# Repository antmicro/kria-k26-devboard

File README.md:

# Antmicro's open source Kria K26 Devboard

Copyright (c) 2022-2023 [Antmicro](https://www.antmicro.com)

## Overview

This project contains open hardware design files for a devkit created for AMD-Xilinx [Kria K26](https://www.xilinx.com/products/som/kria.html) System on Module (SoM).

This development board routes the I/O interfaces from the SoM and provides the necessary power buses.
The design files were prepared in KiCad 7.

## Project structure

The main directory contains KiCad PCB project files, a [LICENSE](LICENSE), and a README.
The remaining files are stored in the following directories:

* `lib` - contains the component libraries
* `img` - contains graphics for this README
* `doc` - contains schematics in pdf form
* `assets` - contains visual assets for showcasing this design on [Open Hardware Portal](https://openhardware.antmicro.com).

## Key Features

* AMD-Xilinx Kria K26 SOM
* Gigabit Ethernet
* DisplayPort output
* 4x USB 3.2 Gen 1 connector
* USB Type-C connector for FTDI JTAG and debug
* M.2 connector (key E) for optional WiFi and Bluetooth connectivity
* 2x 4-lane MIPI CSI-2 camera interface
* PMOD
* SD 3.0 (MicroSD UHS-1)

The board supports multiple power supply scenarios, including:

* PoE (Power over Ethernet)
* USB-C PD (Power Delivery)
* External PSU via DC Jack

The on-board camera connector is electrically compatible with several video accessories created by Antmicro, such as:
 
* [OV9281 Dual Camera Board](https://github.com/antmicro/ov9281-camera-board)
* [SDI-MIPI bridge](https://github.com/antmicro/sdi-mipi-bridge)
* [HDMI-MIPI bridge](https://github.com/antmicro/hdmi-mipi-bridge)

## Block diagram

## License

This project is published under the [Apache-2.0](LICENSE) license.

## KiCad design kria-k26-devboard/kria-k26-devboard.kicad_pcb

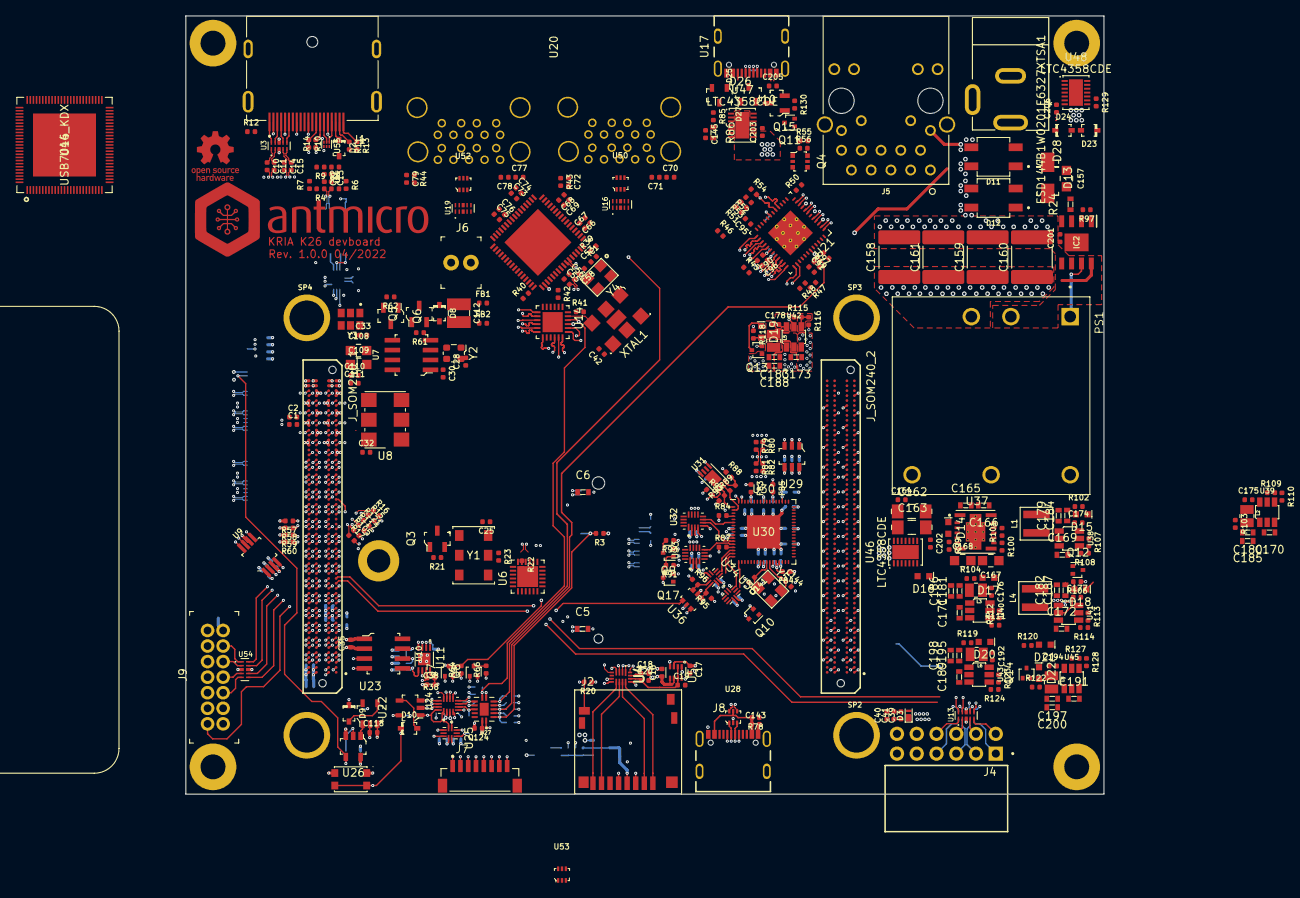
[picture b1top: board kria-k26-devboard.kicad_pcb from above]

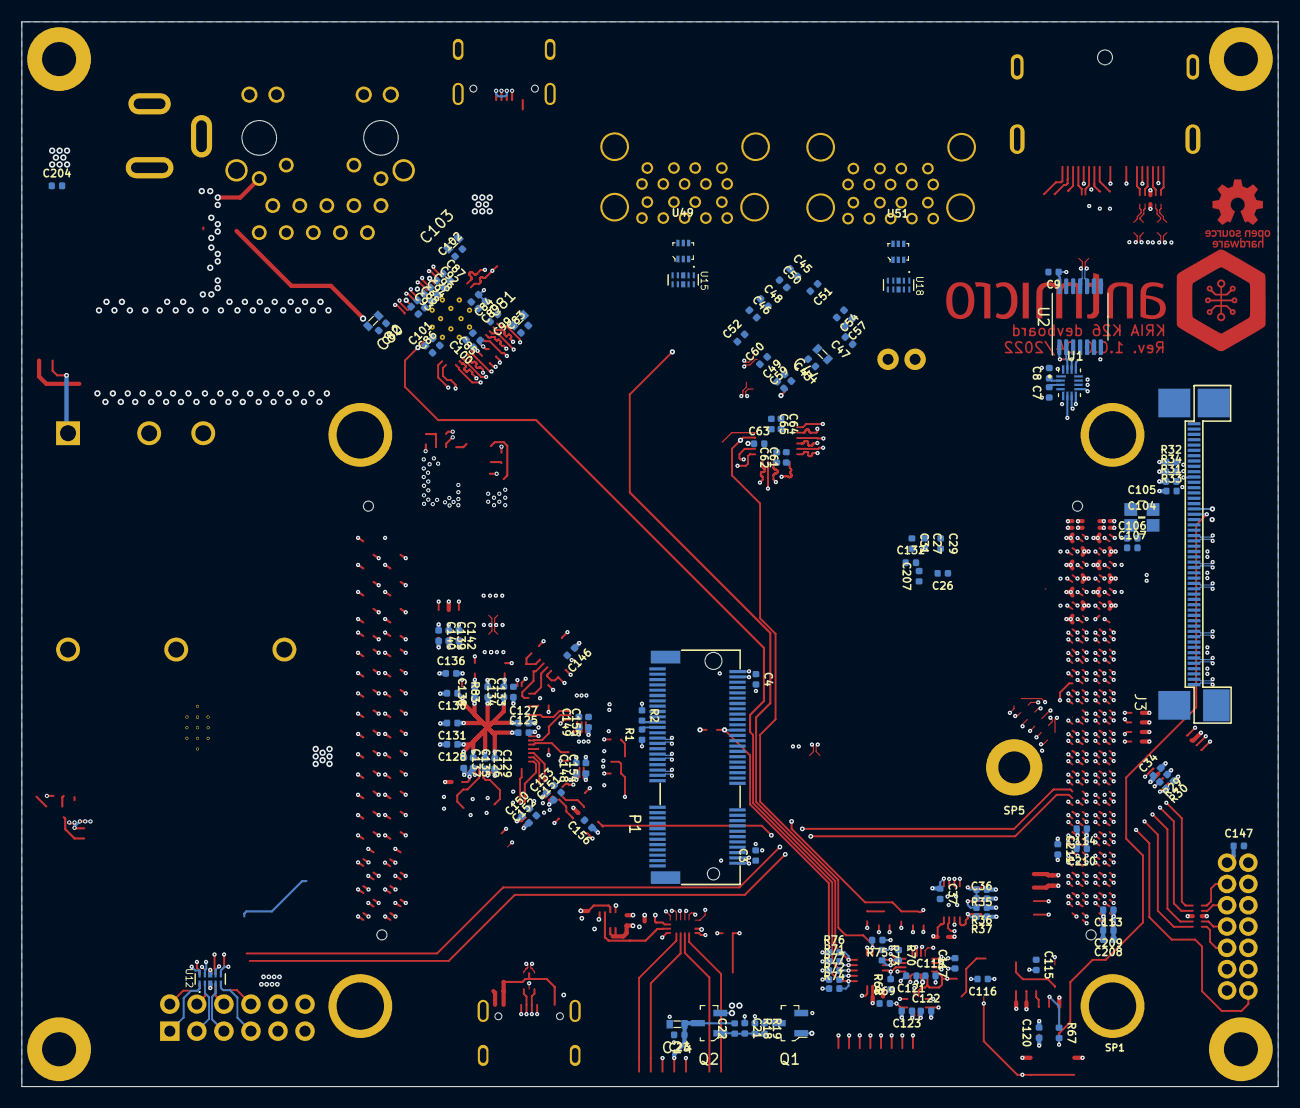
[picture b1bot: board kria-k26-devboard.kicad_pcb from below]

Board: 8 copper layers, 118.0 x 100.0 mm, 469 parts (140 on the bottom side), 378 nets.

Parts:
C1, C2, C3, C4, C7, C8, C9, C10, C11, C12, C13, C14, C15, C16, C17, C18, C19, C20, C23, C25, C26, C27, C28, C29, C30, C31, C32, C33, C34, C35, C37, C38, C40, C41, C42, C45, C46, C47, C48, C49, C50, C51, C52, C54, C55, C56, C57, C59, C60, C61, C62, C63, C65, C66, C67, C68, C69, C72, C73, C74, C75, C76, C79, C89, C90, C91, C92, C93, C94, C95, C96, C97, C107, C111, C113, C114, C117, C118, C119, C120, C121, C122, C123, C124, C125, C126, C127, C128, C129, C130, C131, C132, C133, C134, C135, C137, C138, C139, C140, C142, C146, C147, C148, C149, C150, C151, C152, C153, C154, C155, C156, C174, C175, C176, C177, C178, C192, C194, C201, C202, C203, C204, C207, C209, C211: C_100n_0402; 0402-cap
C5, C6, C24, C44, C80, C81, C103: C_10u_0603; 0603-cap
C21, C22: C_470n_0402; 0402-cap
C36: C_100p_0402; 0402-cap
C39, C43, C84, C85, C86, C87, C88, C98, C99, C100, C101, C106, C110: C_1u_0402; 0402-cap
C53, C58, C141, C144: C_18p_0402; 0402-cap
C64: C_2u2_0402; 0402-cap
C70, C71, C77, C78, C136, C208, C210: C_4u7_0402; 0402-cap
C82, C83, C102: C_10n_0402; 0402-cap
C104, C105, C108, C109, C167, C168: C_47u_0805; 0805-cap
C112: C_1u_1210_100V; 1210-cap
C115, C116: C_47n_0402; 0402-cap
C143, C205, C206: C_100n_0402_50V; 0402-cap
C145: C_33n_0402; 0402-cap
C157: C_100n_0805_100V; 0805-cap
C158, C159, C160, C161: C_22u_2220_100V; 2220-cap
C162, C163: C_47u_16V_1206; 1206-cap
C164: C_100n_0402_16V; 0402-cap
C165, C166, C169, C170, C171, C172, C173, C189, C191: C_10u_25V_0603; 0603-cap
C179, C180, C181, C182, C183, C184, C185, C186, C187, C188, C195, C197, C198, C200: C_22u_0603; 0603-cap
D2: PMEG3010CEJ; SOD-323F
D3: PTVS5V0Z1USKPYL; SOD-964
D8, D9, D10, D23, D24: 1N4148WS; SOD-323F
D11, D12: MB10S
D13: SMAJ58A-13-F; DO-214AC
D14, D15, D16, D17, D18, D19, D20, D21, D22: LG_L29K-G2J1-24-Z; LED_0603
D25, D27: PESD2USB5UV-TR; SOT-23s
D26, D28: ESD144B1W0201E6327XTSA1
FB1, FB2, FB3, FB4, FB5: BLM15PD121SN1D; 0402-res
IC1: USB5534B-5000JZX
IC2: TPS2378DDA; SOIC127P600X170-9N
J1: 47272-0001; MOLEX_47272-0001
J2: 1140084168; MicroSD_1140084168
J3: WE_68715014522
J4: SSW-106-02-G-D-RA; SAMTEC_SSW-106-02-G-D-RA
J5: 5-2337992-8
J6: 22-23-2021; PinHeader_1x2_P2.54mm_Drill1.02mm
J7: BM08B-SRSS-TB-LF-SN
J8, J10: USB4105-GF-A; GCT_USB4105-GF-A
J9: 0878311420; PinHeader_2x7_P2mm_Drill1mm
J11: DC_SOCKET
J_SOM240_1, J_SOM240_2: ADM6-60-01.5-L-4-2-A-TR; SAMTEC_ADM6-60-01.5-L-4-2-A-TR
L1, L4: XEL4030-222MEC; Coilcraft-XEL4030
L2, L3, L5, L6, L8: SRP2010-1R0M; INDC2016X100N
M1: XILINX-KRIA-K26
MP1, MP2, MP3, MP4: PCB_Mount_Hole_3mm_6mm_pad; mounting-hole-3.2mm
N1: oshw_logo; oshw-logo
N2: antmicro_logo; antmicro-logo_scaled_30mm
P1: 2199119-6; TE_1-2199119-6
PS1: PDQE30-Q48-S12-D; PDQE30-Q48
Q1: BSS123; SOT-23-3
Q2: AO3401A; SOT-23-3
Q3, Q6: BSS138-7-F; SOT-23-3
Q4: BSS138DW-7-F; SOT-363
Q5, Q15: PJA3441; SOT-23-3
Q7, Q8, Q9, Q10, Q11, Q12, Q13, Q14, Q17: DTC014TEBTL; SOT-416
R1, R2, R3, R18, R20, R22, R40, R42, R45, R64, R66, R73, R74, R75, R76, R77, R84, R87, R88, R90, R91, R92, R93, R95, R96, R100, R108, R110, R112, R114, R116, R124, R128: R_10k_0402; 0402-res
R4, R5: R_49R9_0402; 0402-res
R6, R46, R48, R101, R115: R_2k49_0402; 0402-res
R7: R_1k5_0402; 0402-res
R8, R9, R13, R61, R62, R68, R69, R70, R71, R72, R85, R130: R_100k_0402; 0402-res
R10, R14, R21: R_1M0_0402; 0402-res
R11, R12, R67, R78, R79, R80, R81, R82: R_0R_0402; 0402-res
R15, R16, R17, R105, R117, R121: R_33R_0402; 0402-res
R19, R38, R102, R106, R118, R119, R122: R_1k_0402; 0402-res
R23, R129: R_100R_0402; 0402-res
R24: R_63R4_0603; 0603-res
R29, R30, R31, R32, R33, R34, R36, R37, R49, R54: R_2k2_0402; 0402-res
R35: R_200k_0402; 0402-res
R39, R83: R_12k_0402; 0402-res
R41: R_8k06_0402; 0402-res
R43, R44, R55, R56: R_330R_0402; 0402-res
R47: R_5k76_0402; 0402-res
R50: R_11k_0402; 0402-res
R51, R52, R53: R_4k7_0402; 0402-res
R57, R58, R59, R60: R_470R_0402; 0402-res
R86: R_15k_0603; 0603-res
R89, R99: R_2k_0402; 0402-res
R97: R_24k9_0402; 0402-res
R103: R_510R_0402; 0402-res
R104, R120: R_68_0402; 0402-res
R107, R123: R_31k6_0402; 0402-res
R109: R_21k5_0402; 0402-res
R111: R_12k4_0402; 0402-res
R113, R127: R_4k99_0402; 0402-res
S1: KMR2; SW_SPST_4.2x2.8
SP1, SP2, SP3, SP4: JSOM-0515-01; SAMTEC_JSOM-0515-01
SP5: 9774015243R
U1, U24, U32, U33: 74AVC4T245RSVRG4; Texas_16-UFQFN
U2: FIN1019MTC; TSSOP-14_4.4x5mm_P0.65mm
U3, U12, U13, U15, U16, U18, U19, U54: TPD4E05U06QDQARQ1
U4: NVT4858HKZ; SOT1161-2
U5: TPS2116DRLR; Texas_DRL0008A
U6: SI53152-A01AGMR; SIL_QFN24_4X4
U7: SN65LVDS1DR; SOIC-8_W3.9mm
U8: XLL736027.000000X; Oscillator_SMD_IDT_JU6-6_7.0x5.0mm_P2.54mm
U9: PI4MSD5V9540BUEX; MSOP-8_W3mm_PITCH0.65mm
U10: PCA9306D_118; SOIC-8_W3.9mm
U11: M24C64-FMC6TG; STM_UFDFPN8DFN8_2X3
U14: USB3310C-CP; Microchip_QFN24_4X4
U17, U20: GSB3112311HR
U21: DP83867CRRGZR; Texas-VQFN-48
U22, U23: TPS3840PH30DBVR; SOT-23-5
U25, U34, U35: SN74AVC2T245RSWR; Texas_RSW0010A
U26: SN74LVC1G125DBVR; SOT-753
U27: 74LCX07BQX; DQFN-14
U28, U49, U50, U51, U52, U53: WE-TVS-82400152; SOT-563
U29: MIC5211-3.3YM6-TR; SOT-23-6
U30: FT4232HPQ; QFN-68_EP_8x8_Pitch0.4mm
U31: 93LC56CT-IMC; DFN-8_2x3mm
U36: NC7WZ07P6X; SOT-363
U37: RPX-4.0-R; Recom_15-PowerBQFN
U38, U39, U40, U41, U42, U43, U45: AP62301WU-7; TSOT23-6
U44: USB7016_KDX; Microchip_VQFN100_EP
U46, U47, U48: LTC4358CDE; Linear_DFN-14
U55: WE-TVS-824012823; WE_DFN1210-6
XTAL1: SIT1602BC-13-18E-24.000000G; SiTIME_SMD-6-1EP
Y1: SIT9120AI-2C3-33E100.000000X; SiTime_5.0x3.2
Y2: ECS-2520MVLC-260-CM-TR; Oscillator_SMD_ECS_2520MV-xxx-xx-4Pin_2.5x2.0mm
Y3: AX3DAF1-125.0000; AX3DAF1
Y4: ABM8G-25.000MHZ-18-D2Y-T; KX-7
Y5: ABM8G-12.000MHZ-18-D2Y-T; KX-7

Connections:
5V_SOM: Q5.2, R61.1
/Camera interface/CAM0_RST: J3.33, J7.6, R67.2, U26.4
/Camera interface/CAM0_VSYNC: J3.32, J_SOM240_1.B17
/Camera interface/CAM1_VSYNC: J3.34, J_SOM240_1.A15
/Camera interface/CCI0_I2C_SCL_3V3: J3.40, R31.2, U9.5
/Camera interface/CCI0_I2C_SDA_3V3: J3.39, R33.2, U9.4
/Camera interface/CCI1_I2C_SCL_3V3: J3.42, R32.2, U9.8
/Camera interface/CCI1_I2C_SDA_3V3: J3.41, R34.2, U9.7
/Camera interface/HDA01: J_SOM240_1.D17, R30.2, U9.1
/Camera interface/HPA00_CC_N: J3.10, J_SOM240_1.C04
/Camera interface/HPA00_CC_P: J3.11, J_SOM240_1.C03
/Camera interface/HPA01_N: J3.7, J_SOM240_1.D08
/Camera interface/HPA01_P: J3.8, J_SOM240_1.D07
/Camera interface/HPA02_N: J3.5, J_SOM240_1.D05
/Camera interface/HPA02_P: J3.6, J_SOM240_1.D04
/Camera interface/HPA03_N: J3.3, J_SOM240_1.C07
/Camera interface/HPA03_P: J3.4, J_SOM240_1.C06
/Camera interface/HPA04_N: J3.1, J_SOM240_1.B05
/Camera interface/HPA04_P: J3.2, J_SOM240_1.B04
/Camera interface/HPA05_CC_N: J3.28, J_SOM240_1.B02
/Camera interface/HPA05_CC_P: J3.29, J_SOM240_1.B01
/Camera interface/HPA06_N: J3.25, J_SOM240_1.A04
/Camera interface/HPA06_P: J3.26, J_SOM240_1.A03
/Camera interface/HPA07_N: J3.23, J_SOM240_1.B08
/Camera interface/HPA07_P: J3.24, J_SOM240_1.B07
/Camera interface/HPA08_N: J3.21, J_SOM240_1.C10
/Camera interface/HPA08_P: J3.22, J_SOM240_1.C09
/Camera interface/HPA09_N: J3.19, J_SOM240_1.D11
/Camera interface/HPA09_P: J3.20, J_SOM240_1.D10
/Clock distribution/GTR_REFCLK0_C2M_N: J_SOM240_1.C48, U7.8
/Clock distribution/GTR_REFCLK0_C2M_P: J_SOM240_1.C47, U7.7
/Clock distribution/GTR_REFCLK1_C2M_N: J_SOM240_1.B50, U8.5
/Clock distribution/GTR_REFCLK1_C2M_P: J_SOM240_1.B49, U8.4
/Clock distribution/GTR_REFCLK2_C2M_N: J_SOM240_1.D54, Y3.5
/Clock distribution/GTR_REFCLK2_C2M_P: J_SOM240_1.D53, Y3.4
/Clock distribution/GTR_REFCLK3_C2M_N: J_SOM240_1.A52, U6.15
/Clock distribution/GTR_REFCLK3_C2M_P: J_SOM240_1.A51, U6.16
/Clock distribution/GTR_REFCLK3_N: P1.49, U6.13
/Clock distribution/GTR_REFCLK3_P: P1.47, U6.14
/Clock distribution/PS_CLK_EN: Q8.3, R66.2, U6.5, U8.1, Y1.1, Y2.1, Y3.1
/Clock distribution/~M2_CLKREQ: P1.53, Q3.1, R1.2, R21.2
/Debug and JTAG/CONN_GND: J9.14, Q9.1, Q17.3, R91.2
/Debug and JTAG/EECLK: R90.2, U30.1, U31.2
/Debug and JTAG/EECS: R92.2, U30.68, U31.1
/Debug and JTAG/EEDATA: R89.1, U30.2, U31.3
/Debug and JTAG/FTDI_EEPROM_WC: Q10.1, U30.46
/Debug and JTAG/FTDI_TCK: U30.6, U32.7
/Debug and JTAG/FTDI_TDI: U30.7, U32.8
/Debug and JTAG/FTDI_TDO: U30.11, U33.6
/Debug and JTAG/FTDI_TMS: U30.12, U32.6
/Debug and JTAG/FTDI_UARTB_RXD: U30.18, U35.8
/Debug and JTAG/FTDI_UARTB_TXD: U30.17, U35.9
/Debug and JTAG/JTAG_TCK_C2M: J9.6, J_SOM240_1.A25, U32.14, U54.2, U54.9
/Debug and JTAG/JTAG_TDI_C2M: J9.10, J_SOM240_1.A24, U32.13, U54.5, U54.6
/Debug and JTAG/JTAG_TDO_M2C: J9.8, J_SOM240_1.A23, U33.15, U54.4, U54.7
/Debug and JTAG/JTAG_TMS_C2M: J9.4, J_SOM240_1.A22, U32.15, U54.1, U54.10
/Debug and JTAG/JTAG_VCCO_ON: U30.13, U33.8
/Debug and JTAG/MIO36: J_SOM240_1.B29, U35.5
/Debug and JTAG/MIO37: J_SOM240_1.B30, U35.4
/Debug and JTAG/PD1_SVBUS: C145.1, R85.2, R86.1, U30.63
/Debug and JTAG/PD_3V3: C140.2, FB3.1, U29.6
/Debug and JTAG/PD_EN: Q11.1, U30.54
/Debug and JTAG/USBB_N: R82.2, U28.4
/Debug and JTAG/USBB_P: R81.2, U28.6
/Debug and JTAG/USBB_VBUS: C143.1, J8.A4_B9, J8.B4_A9, R78.2, U28.5
/Debug and JTAG/USBC_N: D27.1, J10.A7, J10.B7, R80.1
/Debug and JTAG/USBC_P: D27.2, J10.A6, J10.B6, R79.1
/Debug and JTAG/USBC_VBUS: C139.2, C205.1, D26.1, J10.A4_B9, J10.B4_A9, Q15.2, R78.1, R85.1, R130.1, U29.1, U29.3, U29.5
/Debug and JTAG/USB_1V2: C127.2, C129.2, C131.2, C133.2, C137.2, U30.8, U30.25, U30.31, U30.44, U30.66
/Debug and JTAG/USB_3V3: C125.2, C126.2, C128.2, C130.2, C136.1, C142.2, C146.1, C148.1, C149.1, C150.1, C151.1, C153.1, C156.1, FB4.1, FB5.1, R84.1, R87.1, R88.1, R90.1, R91.1, R92.1, R93.1, R95.1, R96.1, U29.4, U30.10, U30.26, U30.39, U30.51, U31.8, U32.3, U33.3, U34.6, U34.7, U35.7, U36.5
/Debug and JTAG/USB_N: R80.2, R82.1, U30.58
/Debug and JTAG/USB_P: R79.2, R81.1, U30.59
/Debug and JTAG/USB_PWRD_VCCIO: U32.4, U32.5, U35.10
/Debug and JTAG/VCC_PD: C134.2, FB3.2, U30.61, U30.64
/Debug and JTAG/VCC_USB: C138.2, FB5.2, U30.57, U34.1, U34.10
/Debug and JTAG/VREGIN: C135.2, FB4.2, U30.30
/Debug and JTAG/XIN: C141.1, U30.27, Y5.1
/Debug and JTAG/XOUT: C144.1, U30.28, Y5.3
/Debug and JTAG/~EEPROM_WC: Q10.3, R38.2, U11.7
/Debug and JTAG/~FTDI_LS_OE: Q17.1, R87.2, U30.14
/Debug and JTAG/~FTDI_PS_POR: U30.15, U34.9
/Debug and JTAG/~FTDI_PS_SRST: U30.16, U34.8
/Debug and JTAG/~FTDI_PWREN: U30.67, U34.2
/Debug and JTAG/~LS_OE: Q9.3, R93.2, U32.1, U32.16, U33.1
/Debug and JTAG/~PS_POR: J7.1, J_SOM240_1.C15, Q7.3, R64.2, U36.4
/Debug and JTAG/~PS_SRST_C2M: J9.13, J_SOM240_1.C16, U36.6
/Display Port/DP_AUX_C_N: C13.1, J1.17, R8.2, U55.1, U55.6
/Display Port/DP_AUX_C_P: C12.1, J1.15, R9.1, U55.2, U55.5
/Display Port/DP_AUX_IN: U1.13, U2.4
/Display Port/DP_AUX_N: C13.2, R5.1, U2.9, U2.11
/Display Port/DP_AUX_OUT: U1.15, U2.2
/Display Port/DP_AUX_P: C12.2, R4.1, U2.10, U2.12
/Display Port/DP_HPD: J1.20, R13.1, U1.12
/Display Port/DP_OE: U1.14, U2.1, U2.8
/Display Port/GTR_DP0_M2C_C_N: C15.1, J1.6, U3.5, U3.6
/Display Port/GTR_DP0_M2C_C_P: C14.1, J1.4, U3.4, U3.7
/Display Port/GTR_DP0_M2C_N: C15.2, J_SOM240_1.B58
/Display Port/GTR_DP0_M2C_P: C14.2, J_SOM240_1.B57
/Display Port/GTR_DP1_M2C_C_N: C11.1, J1.3, U3.2, U3.9
/Display Port/GTR_DP1_M2C_C_P: C10.1, J1.1, U3.1, U3.10
/Display Port/GTR_DP1_M2C_N: C11.2, J_SOM240_1.A48
/Display Port/GTR_DP1_M2C_P: C10.2, J_SOM240_1.A47
/Display Port/MIO27: J_SOM240_1.D29, U1.6
/Display Port/MIO28: J_SOM240_1.D30, U1.9
/Display Port/MIO29: J_SOM240_1.C30, U1.7
/Display Port/MIO30: J_SOM240_1.C31, U1.8
/Ethernet/LED1: Q4.2, U21.46
/Ethernet/LED2: Q4.5, U21.45
/Ethernet/MIO64: J_SOM240_1.D40, U21.29
/Ethernet/MIO65: J_SOM240_1.D41, U21.28
/Ethernet/MIO66: J_SOM240_1.D42, U21.27
/Ethernet/MIO67: J_SOM240_1.C42, U21.26
/Ethernet/MIO68: J_SOM240_1.C43, U21.25
/Ethernet/MIO69: J_SOM240_1.C44, U21.37
/Ethernet/MIO70: J_SOM240_1.B44, U21.32
/Ethernet/MIO71: J_SOM240_1.B45, R45.2, R46.1, U21.33
/Ethernet/MIO72: J_SOM240_1.B46, U21.34
/Ethernet/MIO73: J_SOM240_1.A42, U21.35
/Ethernet/MIO74: J_SOM240_1.A43, U21.36
/Ethernet/MIO75: J_SOM240_1.A44, R47.2, R48.1, U21.38
/Ethernet/MIO76: J_SOM240_1.D44, U21.16
/Ethernet/MIO77: J_SOM240_1.D45, R54.2, U21.17
/Ethernet/POE_VC1: D11.3, J5.11
/Ethernet/POE_VC2: D11.4, J5.12
/Ethernet/POE_VC3: D12.3, J5.13
/Ethernet/POE_VC4: D12.4, J5.14
/Ethernet/TD_A_N: J5.2, U21.2
/Ethernet/TD_A_P: J5.1, U21.1
/Ethernet/TD_B_N: J5.6, U21.5
/Ethernet/TD_B_P: J5.3, U21.4
/Ethernet/TD_C_N: J5.8, U21.8
/Ethernet/TD_C_P: J5.7, U21.7
/Ethernet/TD_D_N: J5.10, U21.11
/Ethernet/TD_D_P: J5.9, U21.10
/Ethernet/~ETH_RESET: J7.5, R77.2, U21.43, U27.4
/I2C /I2C_SCK_3V3: R36.2, U10.6, U11.6
/I2C /I2C_SDA_3V3: R37.2, U10.5, U11.5
/I2C /MIO24_I2C_SCK: J_SOM240_1.C26, U10.3
/I2C /MIO24_I2C_SDA: J_SOM240_1.C27, U10.4
/PCIE M2 key E /GTR_DP3_C2M_N: J_SOM240_1.D50, P1.37
/PCIE M2 key E /GTR_DP3_C2M_P: J_SOM240_1.D49, P1.35
/PCIE M2 key E /GTR_DP3_M2C_C_N: C2.1, P1.43
/PCIE M2 key E /GTR_DP3_M2C_C_P: C1.1, P1.41
/PCIE M2 key E /GTR_DP3_M2C_N: C2.2, J_SOM240_1.C52
/PCIE M2 key E /GTR_DP3_M2C_P: C1.2, J_SOM240_1.C51
/PCIE M2 key E /~M2_PERST: J7.7, P1.52, R3.2, R74.2, U27.2
/PCIE M2 key E /~M2_PEWAKE: P1.55, R2.2
/PMOD/HDA11: J4.1, J_SOM240_1.A17, U12.1, U12.10
/PMOD/HDA12: J4.3, J_SOM240_1.D20, U12.2, U12.9
/PMOD/HDA13: J4.5, J_SOM240_1.D21, U12.4, U12.7
/PMOD/HDA14: J4.7, J_SOM240_1.D22, U12.5, U12.6
/PMOD/HDA15: J4.2, J_SOM240_1.B20, U13.5, U13.6
/PMOD/HDA16_CC: J4.4, J_SOM240_1.B21, U13.4, U13.7
/PMOD/HDA17: J4.6, J_SOM240_1.B22, U13.2, U13.9
/PMOD/HDA18: J4.8, J_SOM240_1.C22, U13.1, U13.10
/Power Supply/DC Input/DC_IN: C206.1, D23.K, D28.1, J11.1, U48.1, U48.2, U48.3, U48.4, U48.11, U48.12, U48.13, U48.14
/Power Supply/DC/DC conventers/DC_MAIN_BUS: C165.1, C166.1, C169.1, C170.1, C171.1, C172.1, C173.1, C189.1, C191.1, C202.1, C203.1, C204.1, R129.1, U37.1, U37.2, U37.14, U38.3, U39.3, U40.3, U41.3, U42.3, U43.3, U45.3, U46.8, U46.9, U46.15, U47.8, U47.9, U47.15, U48.9, U48.15
/Power Supply/DC/DC conventers/SW_PS_1V0: C178.1, L5.1, U42.2
/Power Supply/PoE/POE_12V: C162.1, C163.1, C164.1, PS1.4, U46.1, U46.2, U46.3, U46.4, U46.11, U46.12, U46.13, U46.14
/Power Supply/PoE/POE_ACTIVE: IC2.7, PS1.1
/Power Supply/PoE/VDD_POE_IN: C157.1, C158.1, C159.1, C160.1, C161.1, D11.1, D12.1, D13.K, IC2.1, PS1.3, R97.1
/Power Supply/PoE/VSS_POE_IN: C157.2, D11.2, D12.2, D13.A, IC2.4, IC2.9, R24.2
/Power Supply/Supply ORing/PD_VBUS: Q15.3, U47.1, U47.2, U47.3, U47.4, U47.11, U47.12, U47.13, U47.14
/Power Supply/USB-C socket/USBC_CC1: D25.1, J10.A5
/Power Supply/USB-C socket/USBC_CC2: D25.2, J10.B5
/Power Supply/VCCOEN_PL_M2C: J_SOM240_1.A20, U38.5, U39.5, U40.5, U41.5, U42.5
/Power Supply/VCCOEN_PS_M2C: J_SOM240_1.A19, U43.5, U45.5
/Reset logic/HDA02: J_SOM240_1.D18, R67.1, U26.2
/Reset logic/MIO38: J_SOM240_1.B32, U24.12
/Reset logic/MIO41: J_SOM240_1.A34, U25.5
/Reset logic/MIO43: J_SOM240_1.A36, U24.15
/Reset logic/MIO44: J_SOM240_1.D32, U24.13, U24.14
/Reset logic/PL_RST: U23.1, U26.1
/Reset logic/PS_RST: Q7.1, Q8.1, U22.1, U24.1, U24.16, U25.2
/Reset logic/~SD_CARD_RESET: J7.2, Q1.1, R73.2, U27.10
/Reset logic/~USB_HUB_RESET: IC1.50, J7.4, R76.2, U27.6
/Reset logic/~USB_PHY_RESET: J7.3, R75.2, U14.22, U27.8
/SD 3.0 card/MIO39: J_SOM240_1.B33, U5.4
/SD 3.0 card/MIO45: J2.9, J_SOM240_1.D33, R20.2
/SD 3.0 card/MIO46: J_SOM240_1.D34, R17.1
/SD 3.0 card/MIO47: J_SOM240_1.C34, R105.1
/SD 3.0 card/MIO48: J_SOM240_1.C35, R117.1
/SD 3.0 card/MIO49: J_SOM240_1.C36, R121.1
/SD 3.0 card/MIO50: J_SOM240_1.B36, R15.1
/SD 3.0 card/MIO51: J_SOM240_1.B37, R16.1
/SD 3.0 card/SD_CLK: J2.5, U4.8
/SD 3.0 card/SD_CMD: J2.3, U4.13
/SD 3.0 card/SD_DAT0: J2.7, U4.10
/SD 3.0 card/SD_DAT1: J2.8, U4.9
/SD 3.0 card/SD_DAT2: J2.1, U4.12
/SD 3.0 card/SD_DAT3: J2.2, U4.11
/SD 3.0 card/VCCB: C19.1, C20.1, U4.14, U5.2, U5.7
/USB/GTR_DP2_C2M_C_N: C56.1, IC1.56
/USB/GTR_DP2_C2M_C_P: C55.1, IC1.55
/USB/GTR_DP2_C2M_N: C56.2, J_SOM240_1.B54
/USB/GTR_DP2_C2M_P: C55.2, J_SOM240_1.B53
/USB/GTR_DP2_M2C_N: IC1.59, J_SOM240_1.D58
/USB/GTR_DP2_M2C_P: IC1.58, J_SOM240_1.D57
/USB/MIO52: J_SOM240_1.D36, U14.11
/USB/MIO53: J_SOM240_1.D37, U14.19
/USB/MIO54: J_SOM240_1.D38, U14.13
/USB/MIO55: J_SOM240_1.C38, U14.18
/USB/MIO56: J_SOM240_1.C39, U14.17
/USB/MIO57: J_SOM240_1.C40, U14.16
/USB/MIO58: J_SOM240_1.B40, U14.20
/USB/MIO59: J_SOM240_1.B41, U14.12
/USB/MIO60: J_SOM240_1.B42, U14.10
/USB/MIO61: J_SOM240_1.A38, U14.9
/USB/MIO62: J_SOM240_1.A39, U14.8
/USB/MIO63: J_SOM240_1.A40, U14.7
/USB/USB1_N: IC1.2, U49.3
/USB/USB1_P: IC1.1, U49.1
/USB/USB1_RX_N: IC1.7, U15.1, U15.10, U17.5
/USB/USB1_RX_P: IC1.6, U15.2, U15.9, U17.6
/USB/USB1_TX_N: C66.2, IC1.4
/USB/USB1_TX_P: C67.2, IC1.3
/USB/USB1_VBUS: C70.1, U17.1, U49.5
/USB/USB2_N: IC1.10, U50.3
/USB/USB2_P: IC1.9, U50.1
/USB/USB2_PHY_N: IC1.54, U14.5
/USB/USB2_PHY_P: IC1.53, U14.6
/USB/USB2_RX_N: IC1.15, U16.1, U16.10, U17.14
/USB/USB2_RX_P: IC1.14, U16.2, U16.9, U17.15
/USB/USB2_TX_N: C68.2, IC1.12
/USB/USB2_TX_P: C69.2, IC1.11
/USB/USB2_VBUS: C71.1, U17.10, U50.5
/USB/USB3_N: IC1.18, U51.3
/USB/USB3_P: IC1.17, U51.1
/USB/USB3_RX_N: IC1.23, U18.1, U18.10, U20.5
/USB/USB3_RX_P: IC1.22, U18.2, U18.9, U20.6
/USB/USB3_TX_N: C73.2, IC1.20
/USB/USB3_TX_P: C74.2, IC1.19
/USB/USB3_VBUS: C77.1, U20.1, U51.5
/USB/USB4_N: IC1.25, U52.3
/USB/USB4_P: IC1.24, U52.1
/USB/USB4_RX_N: IC1.30, U19.1, U19.10, U20.14
/USB/USB4_RX_P: IC1.29, U19.2, U19.9, U20.15
/USB/USB4_TX_N: C75.2, IC1.27
/USB/USB4_TX_P: C76.2, IC1.26
/USB/USB4_VBUS: C78.1, U20.10, U52.5
/USB/XIN: C53.1, IC1.62, Y4.1
/USB/XOUT: C58.1, IC1.61, Y4.3
/Xilinx K26 SOM/HDA00_C: J_SOM240_1.D16, R29.2, U9.2
/Xilinx K26 SOM/HDA20: J_SOM240_1.C24, Q6.1, R62.1
/Xilinx K26 SOM/MODE0_C2M: J_SOM240_1.A27, R60.1
/Xilinx K26 SOM/MODE1_C2M: J_SOM240_1.A28, R59.1
/Xilinx K26 SOM/MODE2_C2M: J_SOM240_1.A29, R58.1
/Xilinx K26 SOM/MODE3_C2M: J_SOM240_1.A30, R57.1
/Xilinx K26 SOM/VCCO_HDB: J_SOM240_2.B59, J_SOM240_2.B60
/Xilinx K26 SOM/VCCO_HDC: J_SOM240_2.D59, J_SOM240_2.D60
/Xilinx K26 SOM/VCCO_HPB: J_SOM240_2.A44, J_SOM240_2.B42
/Xilinx K26 SOM/VCCO_HPC: J_SOM240_2.C44, J_SOM240_2.D42
GND: C3.2, C4.2, C5.2, C6.2, C7.1, C8.2, C9.2, C16.2, C17.2, C18.2, C19.2, C20.2, C23.2, C24.2, C25.2, C26.2, C27.2, C28.2, C29.2, C30.2, C31.2, C32.2, C33.2, C34.2, C35.2, C36.2, C37.2, C38.1, C39.2, C40.2, C41.2, C42.2, C43.2, C44.2, C45.2, C46.2, C47.2, C48.2, C49.2, C50.2, C51.2, C52.2, C53.2, C54.2, C57.2, C58.2, C59.2, C60.2, C61.2, C62.2, C63.2, C64.2, C65.2, C70.2, C71.2, C72.2, C77.2, C78.2, C79.2, C80.2, C81.2, C82.2, C83.2, C84.2, C85.2, C86.2, C87.2, C88.2, C89.2, C90.2, C91.2, C92.2, C93.2, C94.2, C95.2, C96.2, C97.2, C98.2, C99.2, C100.2, C101.2, C102.2, C103.2, C104.2, C105.2, C106.2, C107.2, C108.2, C109.2, C110.2, C111.2, C112.2, C113.2, C114.2, C115.2, C116.2, C117.2, C118.2, C119.2, C120.2, C121.2, C122.2, C123.2, C124.2, C125.1, C126.1, C127.1, C128.1, C129.1, C130.1, C131.1, C132.2, C133.1, C134.1, C135.1, C136.2, C137.1, C138.1, C139.1, C140.1, C141.2, C142.1, C143.2, C144.2, C145.2, C146.2, C147.2, C148.2, C149.2, C150.2, C151.2, C152.2, C153.2, C154.2, C155.2, C156.2, C162.2, C163.2, C164.2, C165.2, C166.2, C167.2, C168.2, C169.2, C170.2, C171.2, C172.2, C173.2, C179.1, C180.1, C181.1, C182.1, C183.1, C184.1, C185.1, C186.1, C187.1, C188.1, C189.2, C191.2, C195.1, C197.1, C198.1, C200.1, C202.2, C203.2, C205.2, C206.2, C207.2, C208.2, C209.2, C210.2, C211.2, D3.A, D8.A, D14.2, D15.2, D16.2, D17.2, D20.2, D21.2, D24.K, D25.3, D26.2, D27.3, D28.2, FB2.1, IC1.65, J1.2, J1.5, J1.8, J1.11, J1.16, J2.6, J2.10, J2.~, J4.9, J4.10, J5.19, J5.20, J7.8, J8.A1_B12, J8.B1_A12, J8.S1, J8.S2, J8.S3, J8.S4, J9.1, J9.3, J9.5, J9.7, J9.9, J9.11, J10.B1_A12, J10.S1, J10.S2, J10.S3, J10.S4, J11.3, J_SOM240_1.A02, J_SOM240_1.A05, J_SOM240_1.A08, J_SOM240_1.A11, J_SOM240_1.A14, J_SOM240_1.A18, J_SOM240_1.A21, J_SOM240_1.A26, J_SOM240_1.A33, J_SOM240_1.A37, J_SOM240_1.A41, J_SOM240_1.A45, J_SOM240_1.A46, J_SOM240_1.A49, J_SOM240_1.A50, J_SOM240_1.A53, J_SOM240_1.A54, J_SOM240_1.A57, J_SOM240_1.A58, J_SOM240_1.B03, J_SOM240_1.B06, J_SOM240_1.B09, J_SOM240_1.B12, J_SOM240_1.B15, J_SOM240_1.B19, J_SOM240_1.B23, J_SOM240_1.B27, J_SOM240_1.B31, J_SOM240_1.B35, J_SOM240_1.B39, J_SOM240_1.B43, J_SOM240_1.B47, J_SOM240_1.B48, J_SOM240_1.B51, J_SOM240_1.B52, J_SOM240_1.B55, J_SOM240_1.B56, J_SOM240_1.B59, J_SOM240_1.C01, J_SOM240_1.C02, J_SOM240_1.C05, J_SOM240_1.C08, J_SOM240_1.C11, J_SOM240_1.C14, J_SOM240_1.C17, J_SOM240_1.C21, J_SOM240_1.C25, J_SOM240_1.C29, J_SOM240_1.C33, J_SOM240_1.C37, J_SOM240_1.C41, J_SOM240_1.C46, J_SOM240_1.C49, J_SOM240_1.C50, J_SOM240_1.C53, J_SOM240_1.C54, J_SOM240_1.C57, J_SOM240_1.C58, J_SOM240_1.D03, J_SOM240_1.D06, J_SOM240_1.D09, J_SOM240_1.D12, J_SOM240_1.D15, J_SOM240_1.D19, J_SOM240_1.D23, J_SOM240_1.D27, J_SOM240_1.D31, J_SOM240_1.D35, J_SOM240_1.D39, J_SOM240_1.D43, J_SOM240_1.D47, J_SOM240_1.D48, J_SOM240_1.D51, J_SOM240_1.D52, J_SOM240_1.D55, J_SOM240_1.D56, J_SOM240_1.D59, J_SOM240_2.A01, J_SOM240_2.A02, J_SOM240_2.A05, J_SOM240_2.A06, J_SOM240_2.A09, J_SOM240_2.A10, J_SOM240_2.A13, J_SOM240_2.A16, J_SOM240_2.A19, J_SOM240_2.A22, J_SOM240_2.A25, J_SOM240_2.A28, J_SOM240_2.A31, J_SOM240_2.A34, J_SOM240_2.A37, J_SOM240_2.A40, J_SOM240_2.A43, J_SOM240_2.A45, J_SOM240_2.A49, J_SOM240_2.A53, J_SOM240_2.A57, J_SOM240_2.B03, J_SOM240_2.B04, J_SOM240_2.B07, J_SOM240_2.B08, J_SOM240_2.B11, J_SOM240_2.B14, J_SOM240_2.B17, J_SOM240_2.B20, J_SOM240_2.B23, J_SOM240_2.B26, J_SOM240_2.B29, J_SOM240_2.B32, J_SOM240_2.B35, J_SOM240_2.B38, J_SOM240_2.B41, J_SOM240_2.B43, J_SOM240_2.B47, J_SOM240_2.B51, J_SOM240_2.B55, J_SOM240_2.C01, J_SOM240_2.C02, J_SOM240_2.C05, J_SOM240_2.C06, J_SOM240_2.C09, J_SOM240_2.C10, J_SOM240_2.C13, J_SOM240_2.C16, J_SOM240_2.C19, J_SOM240_2.C22, J_SOM240_2.C25, J_SOM240_2.C28, J_SOM240_2.C31, J_SOM240_2.C34, J_SOM240_2.C37, J_SOM240_2.C40, J_SOM240_2.C43, J_SOM240_2.C45, J_SOM240_2.C49, J_SOM240_2.C53, J_SOM240_2.C57, J_SOM240_2.D03, J_SOM240_2.D04, J_SOM240_2.D07, J_SOM240_2.D08, J_SOM240_2.D11, J_SOM240_2.D14, J_SOM240_2.D17, J_SOM240_2.D20, J_SOM240_2.D23, J_SOM240_2.D26, J_SOM240_2.D29, J_SOM240_2.D32, J_SOM240_2.D35, J_SOM240_2.D38, J_SOM240_2.D41, J_SOM240_2.D43, J_SOM240_2.D47, J_SOM240_2.D51, J_SOM240_2.D55, MP1.1, MP2.1, MP3.1, MP4.1, P1.1, P1.7, P1.18, P1.33, P1.39, P1.45, P1.51, P1.57, P1.63, P1.69, P1.75, P1.M, PS1.6, Q1.2, Q3.2, Q4.1, Q4.4, Q6.2, Q7.2, Q8.2, Q9.2, Q10.2, Q11.2, Q12.2, Q13.2, Q14.2, Q17.2, R7.2, R9.2, R10.2, R11.2, R12.2, R13.2, R14.1, R21.1, R39.2, R41.2, R43.2, R44.2, R46.2, R48.2, R50.2, R57.2, R58.2, R59.2, R60.2, R62.2, R68.1, R69.1, R70.1, R71.1, R72.1, R83.1, R86.2, R101.2, R108.2, R110.2, R112.2, R114.2, R116.2, R124.2, R128.2, S1.1, S1.3, SP1.1, SP2.1, SP3.1, SP4.1, SP5.1, U1.1, U1.5, U1.10, U1.11, U1.16, U2.7, U3.3, U3.8, U4.7, U5.1, U6.4, U6.24, U6.25, U7.4, U8.3, U9.6, U10.1, U11.2, U11.3, U11.4, U11.9, U12.3, U12.8, U13.3, U13.8, U14.1, U14.25, U15.3, U15.8, U16.3, U16.8, U17.4, U17.7, U17.13, U17.16, U18.3, U18.8, U19.3, U19.8, U20.4, U20.7, U20.13, U20.16, U21.49, U22.3, U23.3, U24.4, U24.5, U24.10, U24.11, U25.1, U25.3, U25.4, U25.10, U26.3, U27.7, U28.2, U29.2, U30.3, U30.9, U30.29, U30.69, U31.5, U32.9, U32.10, U32.11, U33.4, U33.5, U33.10, U33.11, U33.12, U33.14, U33.16, U34.3, U35.1, U35.2, U35.3, U36.2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
GNDD: C158.2, C159.2, C160.2, C161.2, IC2.5, IC2.8, PS1.2
unnamed: C21.2, C22.1, Q2.1, R18.2, R19.2
unnamed: C22.2, C23.1, C24.1, J2.4, Q2.3
unnamed: C36.1, R35.2, U10.7, U10.8
unnamed: C64.1, U14.4
unnamed: C66.1, U15.4, U15.7, U17.8
unnamed: C67.1, U15.5, U15.6, U17.9
unnamed: C68.1, U16.4, U16.7, U17.17
unnamed: C69.1, U16.5, U16.6, U17.18
unnamed: C72.1, R43.1, U17.19
unnamed: C73.1, U18.4, U18.7, U20.8
unnamed: C74.1, U18.5, U18.6, U20.9
unnamed: C75.1, U19.4, U19.7, U20.17
unnamed: C76.1, U19.5, U19.6, U20.18
unnamed: C79.1, R44.1, U20.19
unnamed: C112.1, D8.K, FB1.1, Q5.3
unnamed: C115.1, U23.5
unnamed: C116.1, U22.5
unnamed: C174.1, L1.1, U38.2
unnamed: C174.2, U38.6
unnamed: C175.1, L2.1, U39.2
unnamed: C175.2, U39.6
unnamed: C176.1, L3.1, U40.2
unnamed: C176.2, U40.6
unnamed: C177.1, L4.1, U41.2
unnamed: C177.2, U41.6
unnamed: C178.2, U42.6
unnamed: C192.1, L6.1, U43.2
unnamed: C192.2, U43.6
unnamed: C194.1, L8.1, U45.2
unnamed: C194.2, U45.6
unnamed: C201.1, R129.2, U48.8
unnamed: C201.2, C204.2, D23.A, D24.A, U48.7
unnamed: D2.K, J1.18
unnamed: D9.A, U23.4
unnamed: D10.A, U22.4
unnamed: D9.K, D10.K, S1.2, S1.4
unnamed: D14.1, R99.1
unnamed: D15.1, R102.2
unnamed: D16.1, R103.1
unnamed: D17.1, R104.2
unnamed: D18.1, R106.2
unnamed: D18.2, Q12.3
unnamed: D19.1, R118.2
unnamed: D19.2, Q13.3
unnamed: D20.1, R119.2
unnamed: D21.1, R120.2
unnamed: D22.1, R122.2
unnamed: D22.2, Q14.3
unnamed: FB1.2, J6.2
unnamed: FB2.2, J6.1
unnamed: IC1.48, R40.2
unnamed: IC1.64, R39.1
unnamed: IC2.2, R97.2
unnamed: IC2.3, R24.1
unnamed: J1.13, R10.1
unnamed: J1.14, R14.2
unnamed: J1.19, R11.1
unnamed: J3.9, J3.12, J3.15, J3.18, J3.27, J3.30
unnamed: J5.15, R55.2
unnamed: J5.16, Q4.3
unnamed: J5.17, R56.2
unnamed: J5.18, Q4.6
unnamed: J8.A6, J8.B6, U28.1
unnamed: J8.A7, J8.B7, U28.3
unnamed: Q1.3, R19.1
unnamed: Q3.3, R22.2, U6.18
unnamed: Q5.1, Q6.3, R61.2
unnamed: Q11.3, Q15.1, R130.2
unnamed: R4.2, R5.2, R6.2, R7.1
unnamed: R15.2, U4.16
unnamed: R16.2, U4.5
unnamed: R17.2, U4.3
unnamed: R23.1, U6.22, Y1.4
unnamed: R23.2, U6.23, Y1.5
unnamed: R41.1, U14.24
unnamed: R42.2, U14.2
unnamed: R49.2, U21.44
unnamed: R50.1, U21.12
unnamed: R51.1, U21.23
unnamed: R52.1, U21.20
unnamed: R53.1, U21.22
unnamed: R68.2, U24.6, U27.11
unnamed: R69.2, U25.8, U27.1
unnamed: R70.2, U24.7, U27.9
unnamed: R71.2, U24.8, U27.5
unnamed: R72.2, U24.9, U27.3
unnamed: R83.2, U30.60
unnamed: R84.2, U30.4
unnamed: R88.2, R89.2, U31.4
unnamed: R95.2, U34.5, U36.1
unnamed: R96.2, U34.4, U36.3
unnamed: R100.1, R101.1, U37.9
unnamed: R105.2, U4.4
unnamed: R107.2, R108.1, U38.4
unnamed: R109.2, R110.1, U39.4
unnamed: R111.2, R112.1, U40.4
unnamed: R113.2, R114.1, U41.4
unnamed: R115.2, R116.1, U42.4
unnamed: R117.2, U4.1
unnamed: R121.2, U4.2
unnamed: R123.2, R124.1, U43.4
unnamed: R127.2, R128.1, U45.4
unnamed: U7.2, Y2.3
unnamed: U7.3, U7.5, U7.6
unnamed: U14.23, XTAL1.3
unnamed: U17.2, U49.4
unnamed: U17.3, U49.6
unnamed: U17.11, U50.4
unnamed: U17.12, U50.6
unnamed: U20.2, U51.4
unnamed: U20.3, U51.6
unnamed: U20.11, U52.4
unnamed: U20.12, U52.6
unnamed: U37.4, U37.5
unnamed: U37.3, U37.10, U37.11
PL_1V2: C113.1, C197.2, C200.2, C208.1, C209.1, J_SOM240_1.D01, J_SOM240_1.D02, L8.2, Q14.1, R127.1
PL_3V3: C34.1, C39.1, C40.1, C41.1, C114.1, C118.1, C120.1, C195.2, C198.2, C210.1, C211.1, D3.K, J3.47, J3.48, J4.11, J4.12, J_SOM240_1.B13, J_SOM240_1.B14, L6.2, R29.1, R30.1, R31.1, R32.1, R33.1, R34.1, R119.1, R122.1, R123.1, U9.3, U23.2, U26.5
PS_1V0: C94.1, C95.1, C96.1, C97.1, C98.1, C99.1, C100.1, C101.1, C102.1, C103.1, C183.2, C188.2, L5.2, Q13.1, R115.1, U21.6, U21.24, U21.31, U21.42
PS_1V2: C44.1, C46.1, C48.1, C50.1, C51.1, C54.1, C57.1, C59.1, C60.1, C182.2, C187.2, IC1.5, IC1.8, IC1.13, IC1.21, IC1.28, IC1.31, IC1.51, IC1.57, L4.2, Q12.1, R113.1
PS_1V8: C7.2, C17.1, C18.1, C35.1, C42.1, C61.1, C62.1, C63.1, C80.1, C82.1, C84.1, C85.1, C86.1, C89.1, C90.1, C91.1, C119.1, C122.1, C147.1, C152.1, C154.1, C155.1, C181.2, C186.2, J9.2, L3.2, R20.1, R45.1, R47.1, R49.1, R51.2, R52.2, R53.2, R54.1, R64.1, R75.1, R77.1, R104.1, R111.1, U1.3, U1.4, U4.15, U5.3, U10.2, U14.14, U14.15, U14.21, U21.19, U21.30, U21.41, U24.2, U25.6, U32.2, U33.2, U33.13, U35.6, XTAL1.1, XTAL1.4
PS_2V5: C81.1, C83.1, C87.1, C88.1, C92.1, C93.1, C180.2, C185.2, L2.2, R55.1, R56.1, R103.2, R109.1, U21.3, U21.9
PS_3V3: C3.1, C4.1, C5.1, C6.1, C8.1, C9.1, C16.1, C21.1, C25.1, C26.1, C27.1, C28.1, C29.1, C30.1, C31.1, C32.1, C33.1, C37.1, C38.2, C43.1, C45.1, C47.1, C49.1, C52.1, C117.1, C121.1, C123.1, C132.1, C179.2, C184.2, C207.1, D2.A, IC1.16, IC1.34, IC1.52, IC1.63, L1.2, P1.2, P1.4, P1.72, P1.74, Q2.2, R1.1, R2.1, R3.1, R6.1, R8.1, R18.1, R22.1, R35.1, R36.1, R37.1, R38.1, R40.1, R66.1, R73.1, R74.1, R76.1, R102.1, R106.1, R107.1, R118.1, U1.2, U2.14, U5.5, U5.6, U6.1, U6.3, U6.6, U6.12, U6.17, U6.21, U7.1, U8.6, U11.1, U11.8, U22.2, U24.3, U25.7, Y1.6, Y2.4, Y3.6
SOM_5V: C65.1, C124.1, C167.1, C168.1, J3.49, J3.50, J_SOM240_1.A59, J_SOM240_1.A60, J_SOM240_1.B60, J_SOM240_1.C59, J_SOM240_1.C60, J_SOM240_1.D60, R42.1, R99.2, R100.2, U14.3, U27.14, U37.7, U37.8
SOM_5V0: C104.1, C105.1, C106.1, C107.1, C108.1, C109.1, C110.1, C111.1

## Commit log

2022-07-29 Create KiCad project
2022-07-29 Add .gitignore
2022-08-18 Progress in PCB placement
2022-08-18 Add signals to first B2B connector
2022-08-18 Finished PoE part and DC-DC for PS and PL domains
2022-08-18 Replace K26 SOM with virtual component
2022-08-18 Finished USB HUB routing, 45->90 degree angle placement modification
2022-08-18 Fixes on Reset pagae, progress through clock sheet
2022-08-18 Add dummy connectors for mechanical mockup purpouses
2022-08-18 Assign project name and revision
2022-08-18 Added and connected USB PHY and HUB, created schematic sheet for PCIE M2 key E
2022-08-18 Finished adding signals to connector, create hierarchical schematic sheet structure
2022-08-18 First sketches of POE part of supply
2022-08-18 Added second ETH interface, connect POE PSE
2022-08-18 Add USB switches to schematic
2022-08-18 Added signal ESD input protection for USB PD CC lines
2022-08-18 fixed an issue with reset logic (Mixed PS and PL domain on OD buffer), extended the logic circuit to support M.2 PERST# (reset for PCIe WIFI), fixed the polarity of the camera control signal CAM_RST 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
2022-08-18 Component size optimization, SOM connector fanout, routing of camera interface
2022-08-18 Finished DP schematic sheet
2022-08-18 Improvments in matching
2022-08-18 Finished reset logic, added crystal gen. to USB PHY, create power toggle for SD 3.0
2022-08-18 Finished OR'ing controller, supply schematic was arranged hierarhically
2022-08-18 Fixed DP_AUX differential pair connection
2022-08-18 Initial placement of power supply
2022-08-18 Added Led voltage indicator, fan circuit. Tidied up supply and SOM sheet
2022-08-18 Add 0 Ohm for PoE PSE Midspan configuration
2022-08-18 Optimization of power planes, fixed missing capacitors on USB 3.0, unify shields, polishing of layout
2022-08-18 Added finished i2c (wirh eeprom) and pmod sheet. Added JTAG connector with collision avoidance logic
2022-08-18 Removed PL_1V2 DC-DC, Routed: signalling voltage selector for SD 3.0, reset signals and DC-DC enables, VSYNC, ETH connector diff. pairs, missing USB 3.0 diff. pair. Created planes for PoE adnd DC_MAI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
2022-08-18 Finished initial component placement
2022-08-18 Progress in USB HUB routing
2022-08-18 Reconnected USB 2.0 PHY
2022-08-18 Finished PCIe and Camera interface part
2022-08-18 Added supply ESD input protection for USB and DC barrel jack
2022-08-18 Updated strap configuration to match single ETH interface
2022-08-18 Replaced USB HUB to 6 port on the PCB, USB 3 connector fanout and routing
2022-08-18 Finished tidying up the schematic
2022-08-18 Finished Power planes and overall connectivity
2022-08-18 I2C 45->90 degree angle placement modification
2022-08-18 PMOD, SD 3.0, PCIE and DP initial routing, optimized USB 2.0 and ETH signals routing
2022-08-18 Added Clock and Reset sheets
2022-08-18 Fixed VSS connection for OSC and LED pin in PoE POS section, first update of ETH schematic
2022-08-18 Added logic level direction marking for better clarity
2022-08-18 Removed PoE PSE and second ETH interface
2022-08-18 Add connector and standoffs, position those parts on PCB
2022-08-18 Fixed library reference, USB switcch replaced (4 to 6 ports)
2022-08-18 Progress on Debug sheet
2022-08-18 Fixed possible FTDI-USB backfeeding issue, finished PS and FTDI power planes creation, finished routing of FTDI/Debug part
2022-08-18 Initial routing of ETH and USB 2.0 interface, debug socket USB replaced to USB-C, added stud for M2
2022-08-18 Misc. signals routing, routed REF_CLK's, PS Power plane creation
2022-08-18 Finished ETH part of the schematic
2022-08-18 Replaced PCIe clock generation (LVDS to HCSL), Clock component size optimization for USB, Optimized ESD protection for PD USB, placed and routed new clock circuitry, clock signals recalculated to 100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
2022-08-18 Routed USB debug part, DP AUX, Supply for SD 3.0, improved decoupling. Other minor improvments
2022-08-18 Routed I2C, JTAG, PS reset, remaining differential pairs. Component optimization
2022-08-18 Progress on Display port sheet, signal assigment for PCIe M.2
2022-08-18 Routed PS reset, improved SOM fanout, routed remaing SD 3.0 traces, component size optimization
2022-08-18 Updated USB sheet, finished SD 3.0 interface
2022-08-18 Finished length matching and deskewing high speed traces
2022-08-18 Added 5A@4A DC-DC, tiedied up and finished power supply schematic
2022-08-18 Update power supply
2022-08-18 Finished Debug and JTAG schematic
2022-08-18 Finished clock sheet
2022-08-18 Fixed ref. designators on top, added LED marking
2022-08-18 Fixes introduced after initial review, length matching double checked with external plugin
2022-08-18 Finished length matching
2022-08-18 Reconnected all HS traces after via migration, re-matched and deskewed all HS signals. Further improved polygons (clearance and copper balance), started to place designators on silkscreen
2022-08-18 Changed via size
2022-08-18 Applied review suggestions, fixed DRC after via migration
2022-08-18 Fixed desynchronization after kicad crash, finished cleaning after 4A DC-DC replacement
2022-08-18 Fixed DRC on the old settings, changed via size to avoid desigesign to be not poolable, doubled POE capacitors
2022-08-18 Modified TPD4E05U06QDQARQ1 symbol to avoid misconnections on the schematic
2022-08-18 Applied schematic review suggestions
2022-08-18 Replaced 4A DC-DC conventer, finished cleaning after replacement
2022-08-18 Finished PCB
2022-08-18 Fixed missing USB - M2 connection, finishing touches of PCB
2022-08-18 Adjusted priority of one GND polygon
2022-08-18 Finished implementing changes after the review, fixed ETH led connections, length matching fixed and double checked with external script
2022-08-18 Generated gerber files
2022-08-18 Fixed issues found after PCB manufacturer validation
2022-08-18 Corrected layer table
2022-08-18 Finished PCB after the review changes
2022-08-18 Locklib+ added layer table
2022-08-18 Generated final production gerber files for rev. 1.0 0 after PCB manufacturer feedback
2022-08-18 Corrected one differential pair, final order gerber
2022-08-18 Added README
2022-08-18 Generated final gerbers for rev. 1.0.0 after last cosmetic changes, created .zip package ready to send to PCB manufacturer
2022-08-18 Added picture to Readme, fixed dir in dir structure
2022-08-18 Fixed camera I2C crossed connection on the PCB
2022-08-18 Removed backup files
2022-08-18 Added Shutdown pulldown on the PCB, re-tuned DP aux signals after the change
2022-08-18 Fixed wrong footprint assigment for L4 and L7, PCB changed to fit proper inductor footprints. Fixed R22 missing lib
2022-08-18 Fixed camera I2C crossed connection on schematic
2022-08-18 Added .gitignore
2022-08-18 Added Shutdown pulldown on the Schematic
2022-08-18 Updated crystal library: fixed ECS-2016MV-240-BN-TR3 and ECS-2016MV-250-CN-TR3 MPN
2022-08-18 Replaced lib symbol for SN74AVC2T245RSWR to avoid direction confusion
2022-08-18 Added license file
2022-08-18 Replaced FTDI EEPROM to 93LC66BT, Project migrated to Kicad 6
2022-08-18 Fixed 1140084168 lib causing errors, reconfigure and clear DRC after migration to KiCad 6
2022-08-18 Fixed U45 direction issue
2022-08-18 Loclib of project in KiCad 6 format. Removed old KiCad 5 files
2022-08-18 Unified indication LED intensity
2022-08-18 Add 3d model to PinHeader_1x2
2022-08-18 Cosmetic changes after migration to KiCad 6
2022-08-18 Updated J6
2022-08-18 Locked J3, Cleared DRC warnings, added GND vias near ETH diff. pairs to improve signal integrity
2022-08-18 Several cosmetic changes. Corrected R177, R122, R124. Loclib
2022-08-18 Sync PCB with schematic, after library fix
2022-08-18 Bumped Rev to 1.1.0 on schematic, update tables
2022-08-18 Removed USBB_VBUS from U37 ESD diode
2022-08-18 Added Antmicro and OSHW logos o schematics. Removed one more file from KiCad 5 version
2022-08-18 Corrected README, added 3D model of WE_DFN1210-6
2022-08-18 Added cosmetic changes to schematics (e.g. position of labels, designators)
2022-08-18 Corrected labels on the schematics
2022-08-18 Clean img folder, update readme
2022-08-18 Remove fab folder, remove it from README
2022-08-18 Remove KiCad5 related files, remove reset logic png
2022-08-26 README: fix naming convention
2022-10-19 Notes added by 'git notes add'
2022-12-02 Added missing capacitors to ethernet jack
2022-12-02 Fixed DRC
2022-12-02 Fixed footprints
2022-12-02 loclib
2023-03-08 Finish adding 0Ohm DC-DC output resistor
2023-03-08 Adjust ETH GND caps routing, improve stecil for solderability
2023-03-08 Add 0Ohm DC-DC output resistor WiP
2023-03-08 Replace 5V DC-DCs output capacitors to 16V rated ones
2023-03-08 Fix further issues after EC validation
2023-03-08 Add FWUEN button, add testpoints on debug signals
2023-03-08 Add CC2 5K1 pulldown
2023-03-08 Add missing USB7016 TEST1 pin pull-up
2023-03-08 Add mandatory pullup to TPS2116 status signal
2023-03-08 Add test point for I2C, fix MIO25_I2C_SDA naming on i2c sheet
2023-03-08 Bump date and revision
2023-03-08 Fix via inner annular ring
2023-03-08 Clear DRC after modifications
2023-03-08 Loclib of the project
2023-03-08 Added 4u7 to FTDI Vregout
2023-03-08 Export schematic changes to PCB, fix R15 footprint
2023-03-08 Add PCB SHA deadbeef
2023-03-08 Fix TPS2066 symbol
2023-03-08 Fix swapped OE signals on 100MHz PCIe clock generator
2023-03-08 Change USB debug connector to DNP by default
2023-03-08 Replace FTDI 3V3 Regulator
2023-03-08 Fix TX/RX cross on M.2 Key E
2023-03-08 Fix 93LC66BT-IMC symbol
2023-03-08 Add test points on FTDI CDBUS
2023-03-08 Finish implementing review changes on schematic. Push to PCB
2023-03-08 Layout power plane and signal optimizations
2023-03-08 Add optional pulldown for 26MHz LVDS oscillator output
2023-03-08 Fix SN74AVC2T245RSWR symbol and cross on U45
2023-03-08 Add decoupling to cammera and DP connector, schematic cleanup
2023-03-08 Fix USB3310C symbol
2023-03-08 Implement changes on PCB
2023-03-08 Minor changes after Gerber level review
2023-03-08 Fix the inner annular ring
2023-03-08 Add Block diagram, update readme
2023-03-08 Fix block diagram link
2023-03-08 Add fiducials
2023-03-22 Add JSOM-0515-01 standoff simplified 3D model
2023-03-31 README: minor fixes, add OSP badge
2023-06-30 Improve RT6236AHGQUF footprint
2023-06-30 Fix swapped reference designators on the silkscreen
2023-06-30 Updated RT6236AHGQUF foorprint assigment on schematic
2023-06-30 Bump revision
2023-06-30 Fix fan logic inversion
2023-06-30 Bom optimization
2023-10-18 Introduce component standardization
2023-10-18 Clear DRC
2023-10-18 Cleanup
2023-10-18 Clear ERC
2023-10-18 Update PCB schematic
2023-10-18 Update PCB SHA marking and board revision date
2023-10-19 Add assets from job 741368
2023-10-19 Add schematic PDF from job 740999
2023-10-20 Update PDF schematic
2023-10-30 [#50456] Increase stud clearance to 0.6mm, bump revision
2023-10-30 [#47975] Add missing ESD diode pass for USB 3.0 and DP interfaces, bump revision
2023-11-02 Replace studs, fix PMOD ESD diode pass, bump revision
2023-11-02 Fix studs clereance after replacing
2023-11-02 Fix loclib (missing parent footprints)
2024-03-22 [#56935] Update symbol/footprint links; Migrate to KiCad 7
2024-03-22 [#56935] Update J11 DC-jack footprint from lib
2024-03-25 Upload assets
2024-03-26 [#56935] Fix missing highlights in OHP
2024-03-26 [#56935] Loclib
2024-03-26 [#56935] Bump revision & date
2024-03-27 Update assets
2024-03-28 [#56935] Correct errors reported by DRC
2024-03-28 [#56935] Update logo position on pages converted from A4 to A3
2024-03-28 [#56935] Remove duplicated fp-lib-table entry
2024-03-28 [#56935] Update DRC rules
2024-03-28 [#56935] Add missing connections under U41
2024-03-28 [#56935] Cleanup DRC
2024-04-03 README update
2024-09-11 Photo vs render assets
2024-09-12 Refresh assets
2025-01-23 [#71054] Update assets for ohp

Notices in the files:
parts and their libraries:
Copyright 2021 Accelerated Designs. All rights reserved.
